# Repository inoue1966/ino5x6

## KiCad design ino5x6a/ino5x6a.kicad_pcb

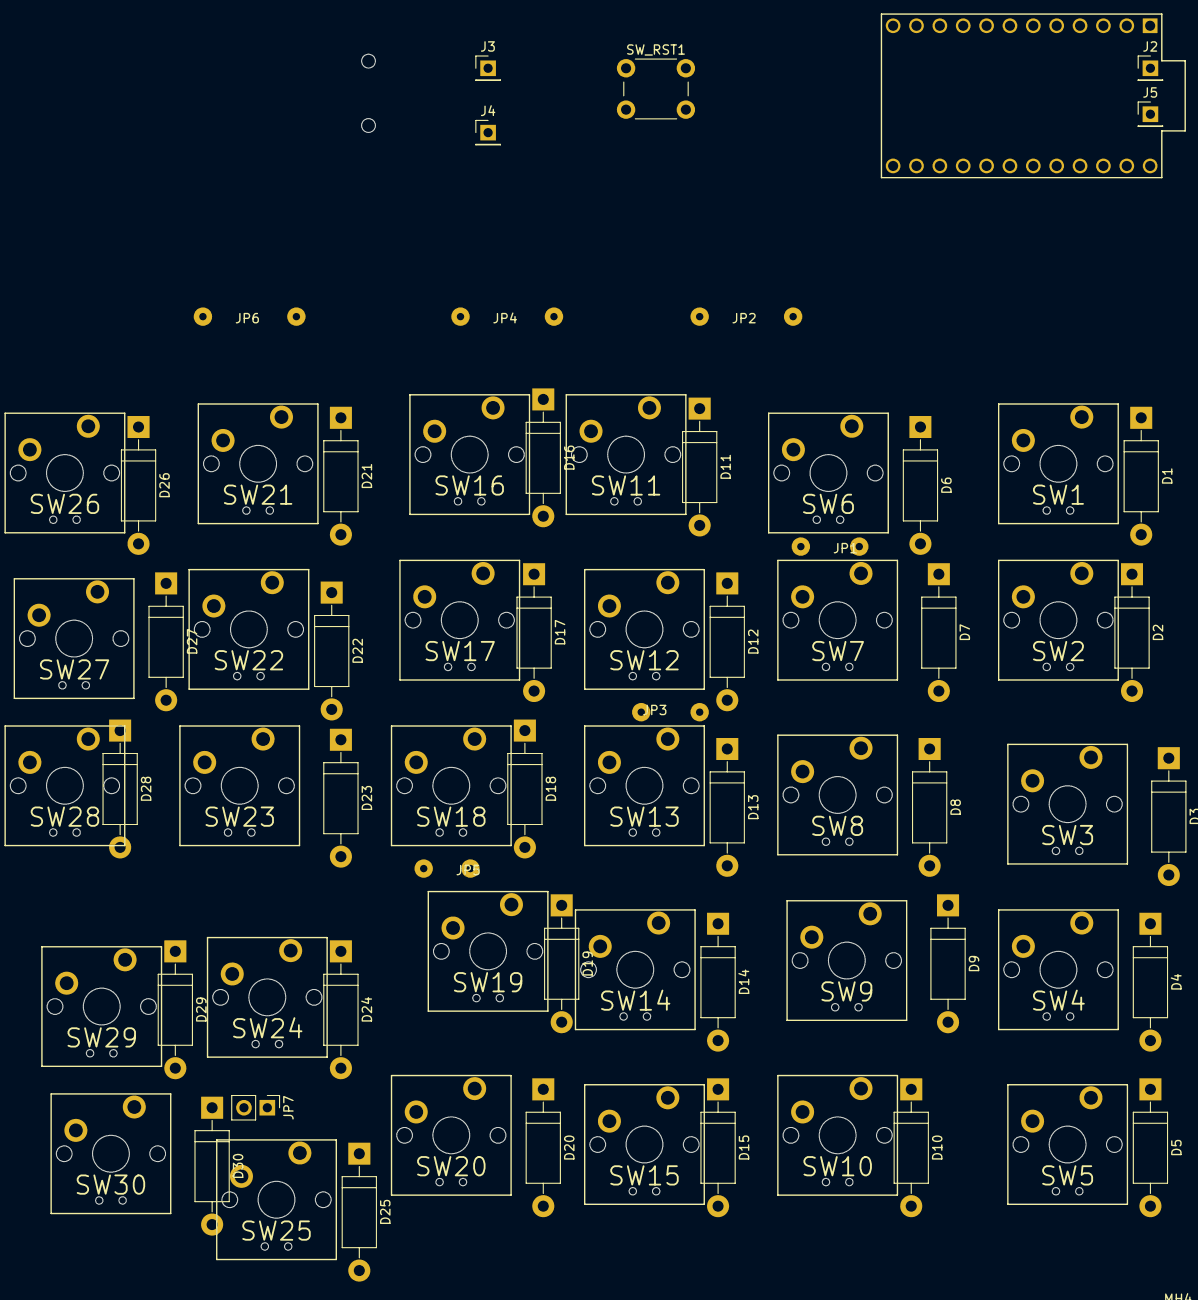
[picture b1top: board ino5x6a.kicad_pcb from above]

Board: 2 copper layers, 78 parts (1 on the bottom side), 54 nets, no tracks yet.

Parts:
D1, D2, D3, D4, D5, D6, D7, D8, D9, D10, D11, D12, D13, D14, D15, D16, D17, D18, D19, D20, D21, D22, D23, D24, D25, D26, D27, D28, D29, D30: DIODE; D_DO-15_P12.70mm_Horizontal
J1: Conn_01x04_Male; PJ320D_3.5mm_Jack
J2, J3, J4, J5: Conn_01x01_Male; Pin_Header_Straight_1x01_Pitch2.54mm
JP1, JP2, JP3, JP4, JP5, JP6: Jumper_2_Bridged; WireConnection_0.80mmDrill
JP7: Jumper_2_Bridged; Pin_Header_Straight_1x02_Pitch2.54mm
MH1, MH2, MH3, MH4: MountingHole; MountingHole_3.2mm_M3
SW1, SW2, SW3, SW4, SW5, SW6, SW7, SW8, SW9, SW10, SW11, SW12, SW13, SW14, SW15, SW16, SW17, SW18, SW19, SW20, SW21, SW22, SW23, SW24, SW25, SW26, SW27, SW28, SW29, SW30: SW_Push; switch
SW_RST1: SW_Push; SW_PUSH_6mm
U1: ProMicro

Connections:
/col0: SW1.1, SW2.1, SW3.1, SW4.1, SW5.1, U1.18
/col1: JP1.1, SW6.1, U1.17
/col2: JP2.1, U1.16
/col3: JP4.1, U1.15
/col4: JP6.1, U1.14
/col5: SW26.1, SW27.1, SW28.1, SW29.1, SW30.1, U1.13
/row0: D1.2, D6.2, D11.2, D16.2, D21.2, D26.2, U1.7
/row1: D2.2, D7.2, D12.2, D17.2, D22.2, D27.2, U1.9
/row2: D3.2, D8.2, D13.2, D18.2, D23.2, D28.2, U1.10
/row3: D4.2, D9.2, D14.2, D19.2, D24.2, D29.2, U1.11
/row4: D5.2, D10.2, D15.2, D20.2, D25.2, D30.2, U1.12
/sda: J1.2, U1.6
GND: J1.4, SW_RST1.2, U1.3, U1.4, U1.23
unnamed: D1.1, SW1.2
unnamed: D2.1, SW2.2
unnamed: D3.1, SW3.2
unnamed: D4.1, SW4.2
unnamed: D5.1, SW5.2
unnamed: D6.1, SW6.2
unnamed: D7.1, SW7.2
unnamed: D8.1, SW8.2
unnamed: D9.1, SW9.2
unnamed: D10.1, SW10.2
unnamed: D11.1, SW11.2
unnamed: D12.1, SW12.2
unnamed: D13.1, SW13.2
unnamed: D14.1, SW14.2
unnamed: D15.1, SW15.2
unnamed: D16.1, SW16.2
unnamed: D17.1, SW17.2
unnamed: D18.1, SW18.2
unnamed: D19.1, SW19.2
unnamed: D20.1, SW20.2
unnamed: D21.1, SW21.2
unnamed: D22.1, SW22.2
unnamed: D23.1, SW23.2
unnamed: D24.1, SW24.2
unnamed: D25.1, SW25.2
unnamed: D26.1, SW26.2
unnamed: D27.1, SW27.2
unnamed: D28.1, SW28.2
unnamed: D29.1, SW29.2
unnamed: D30.1, SW30.2
unnamed: J1.3, J3.1
unnamed: J2.1, U1.1
unnamed: JP1.2, SW7.1, SW8.1, SW9.1, SW10.1
unnamed: JP2.2, JP3.1, SW11.1, SW12.1
unnamed: JP3.2, SW13.1, SW14.1, SW15.1
unnamed: JP4.2, JP5.1, SW16.1, SW17.1, SW18.1
unnamed: JP5.2, SW19.1, SW20.1
unnamed: JP6.2, JP7.1, SW21.1, SW22.1, SW23.1, SW24.1
unnamed: JP7.2, SW25.1
unnamed: SW_RST1.1, U1.22
VCC: J1.1, J4.1, J5.1, U1.21

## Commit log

2018-09-16 first
2018-09-16 一応出来たがおかしい
2018-09-16 ジャックの左右反転
2018-09-16 やっぱり合ってた
2018-09-17 Readme.md
2018-09-17 ディレクトリ構成変更
2018-09-17 反対側用プロジェクト
2018-09-17 配置の厳密化
2018-09-17 クリアランスと太さを0.3に
